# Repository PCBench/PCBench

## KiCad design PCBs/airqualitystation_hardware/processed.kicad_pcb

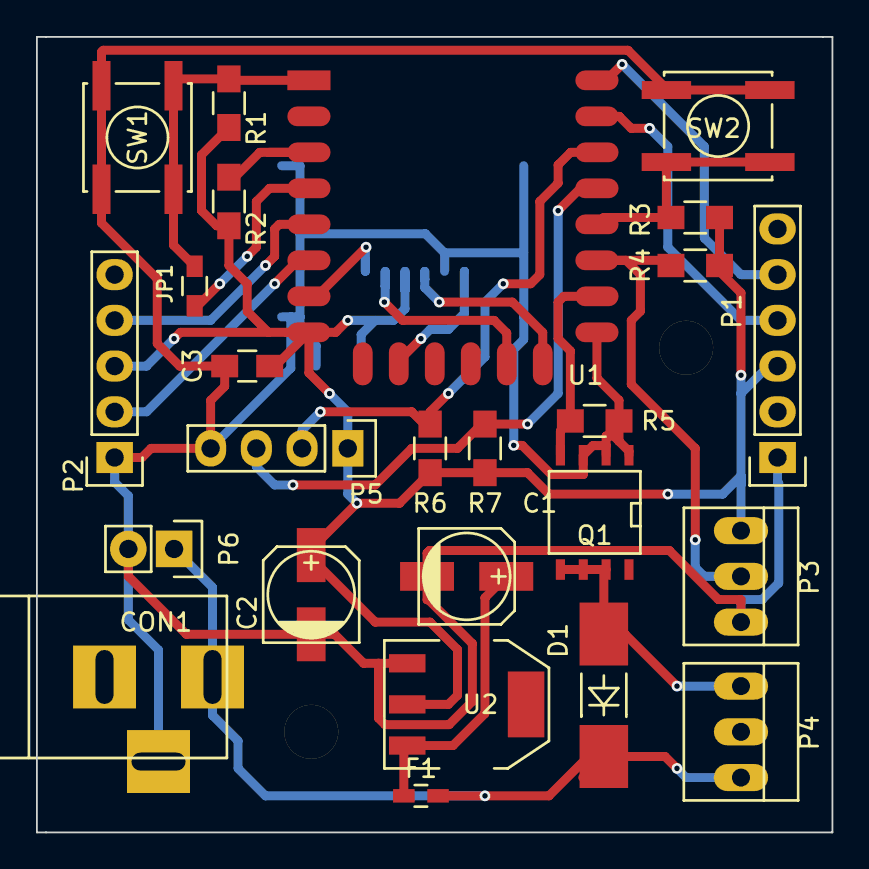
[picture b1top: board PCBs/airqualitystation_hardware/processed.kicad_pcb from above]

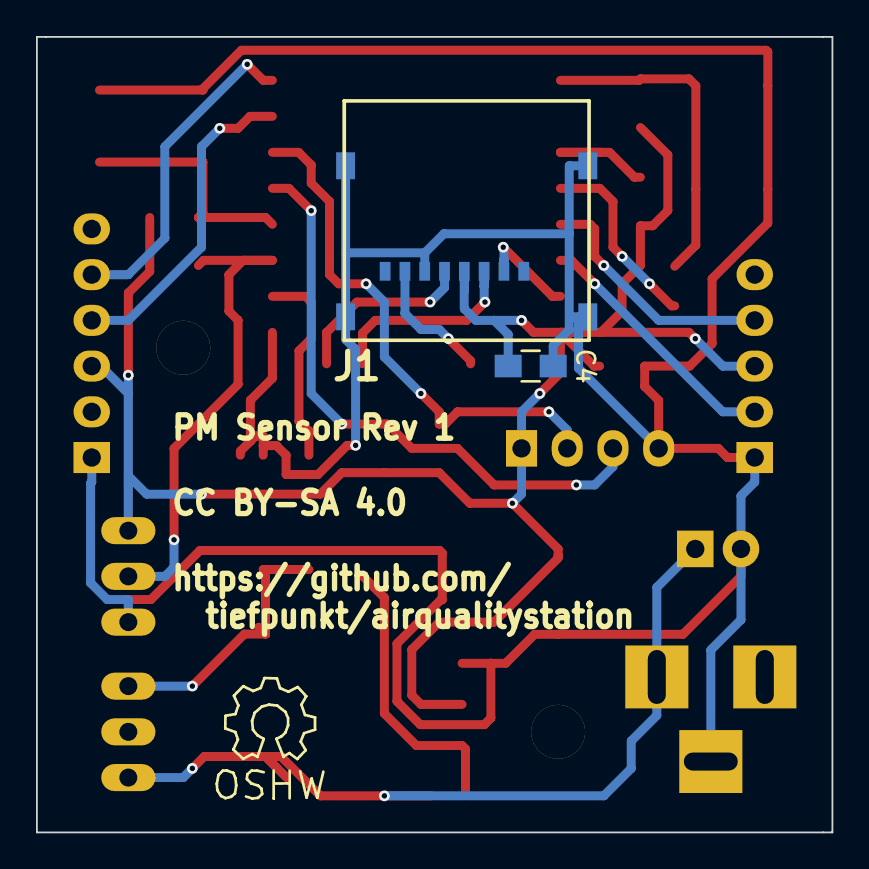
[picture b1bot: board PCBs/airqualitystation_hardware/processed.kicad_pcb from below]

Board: 2 copper layers, 44.2 x 44.2 mm, 27 parts (2 on the bottom side), 21 nets.

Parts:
C1, C2: 10µ; c_elec_5x5.3
C3, C4: 100n; C_0805_HandSoldering
CON1: Power; BARREL_JACK
D1: D; MELF_Handsoldering
F1: 0.1A; C_0603_HandSoldering
J1: MicroSD; MICRO_SD_HINGE_AMP
JP1: Sleep; R_0603_HandSoldering
P1: FTDI ESP; Pin_Header_Straight_1x06
P2: PPD42NS; Pin_Header_Straight_1x05
P3: DHT22; PINHEAD1-3
P4: Fan; PINHEAD1-3
P5: I2C; Pin_Header_Straight_1x04
P6: 5-9V; Pin_Header_Straight_1x02
Q1: IRF7401; SOIC-8-N
R1, R2, R3, R4, R5, R6, R7: 10k; R_0805_HandSoldering
SW1: Reset; SW_SPST_EVPBF
SW2: Flash; SW_SPST_EVPBF
U1: ESP-12E
U2: TS 1117 BCW33; SOT-223

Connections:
+9V: CON1.1, D1.1, F1.1, P4.3, P6.1
GND: C1.2, C2.2, C3.2, C4.2, CON1.3, J1.6, J1.SHLD, P1.1, P2.1, P3.3, P5.4, P6.2, Q1.1, Q1.2, Q1.3, R5.2, SW1.2, SW2.2, U1.15, U2.1
unnamed: C1.1, F1.2, U2.3
unnamed: D1.2, P4.1, Q1.5, Q1.6, Q1.7
unnamed: J1.2, U1.7
unnamed: J1.3, U1.13
unnamed: J1.5, U1.14
unnamed: J1.7, U1.10
unnamed: JP1.1, U1.4
unnamed: JP1.2, R1.2, SW1.1, U1.1
unnamed: P1.4, U1.21
unnamed: P1.5, U1.22
unnamed: P2.2, U1.6
unnamed: P2.4, U1.5
unnamed: P3.2, R4.2, U1.17
unnamed: P5.2, R6.2, U1.20
unnamed: P5.3, R7.2, U1.19
unnamed: Q1.4, R5.1, U1.16
unnamed: R2.2, U1.3
unnamed: R3.2, SW2.1, U1.18
VCC: C2.1, C3.1, C4.1, J1.4, P1.3, P2.3, P3.1, P5.1, R1.1, R2.1, R3.1, R4.1, R6.1, R7.1, U1.8, U2.2

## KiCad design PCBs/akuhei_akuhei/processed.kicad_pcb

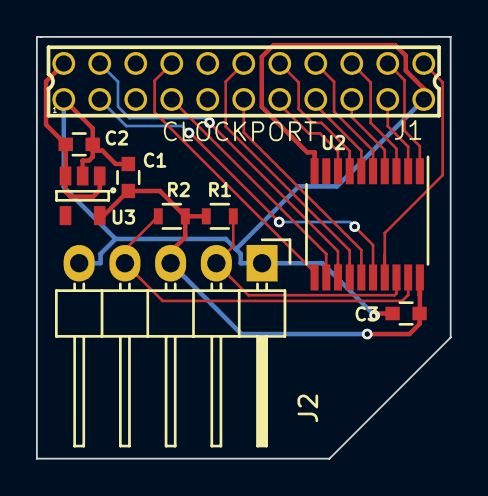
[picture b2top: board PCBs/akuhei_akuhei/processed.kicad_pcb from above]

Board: 2 copper layers, 23.0 x 23.4 mm, 9 parts (0 on the bottom side), 20 nets.

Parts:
C1: 1uF; C_0603
C2: 0.1uF; C_0603
C3: 100nF; C_0603
J1: CLOCKPORT; 87758-2216
J2: I2C; Pin_Header_Angled_1x05
R1, R2: 4.7k; R_0603
U2: PCA9564; TSSOP-20_4.4x6.5mm_Pitch0.65mm
U3: TLV70233DBV; SOT-23-5

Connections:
+3V3: C1.1, C3.1, J2.3, R1.2, R2.2, U2.20, U3.5
+5V: C2.1, J1.2, U3.1, U3.3
/A1: J1.12, U2.14
/A2: J1.11, U2.15
/D0: J1.20, U2.1
/D1: J1.19, U2.2
/D2: J1.18, U2.3
/D3: J1.17, U2.4
/D4: J1.16, U2.5
/D5: J1.15, U2.6
/D6: J1.14, U2.7
/D7: J1.13, U2.8
CP_CS: J1.4, U2.13
CP_INT: J1.3, U2.16
CP_IORD: J1.7, U2.12
CP_IOWR: J1.8, U2.11
CP_RESET: J1.22, U2.17
GND: C1.2, C2.2, C3.2, J1.1, J1.21, J2.1, J2.5, U2.10, U3.2
SCL: J2.2, R1.1, U2.18
SDA: J2.4, R2.1, U2.19

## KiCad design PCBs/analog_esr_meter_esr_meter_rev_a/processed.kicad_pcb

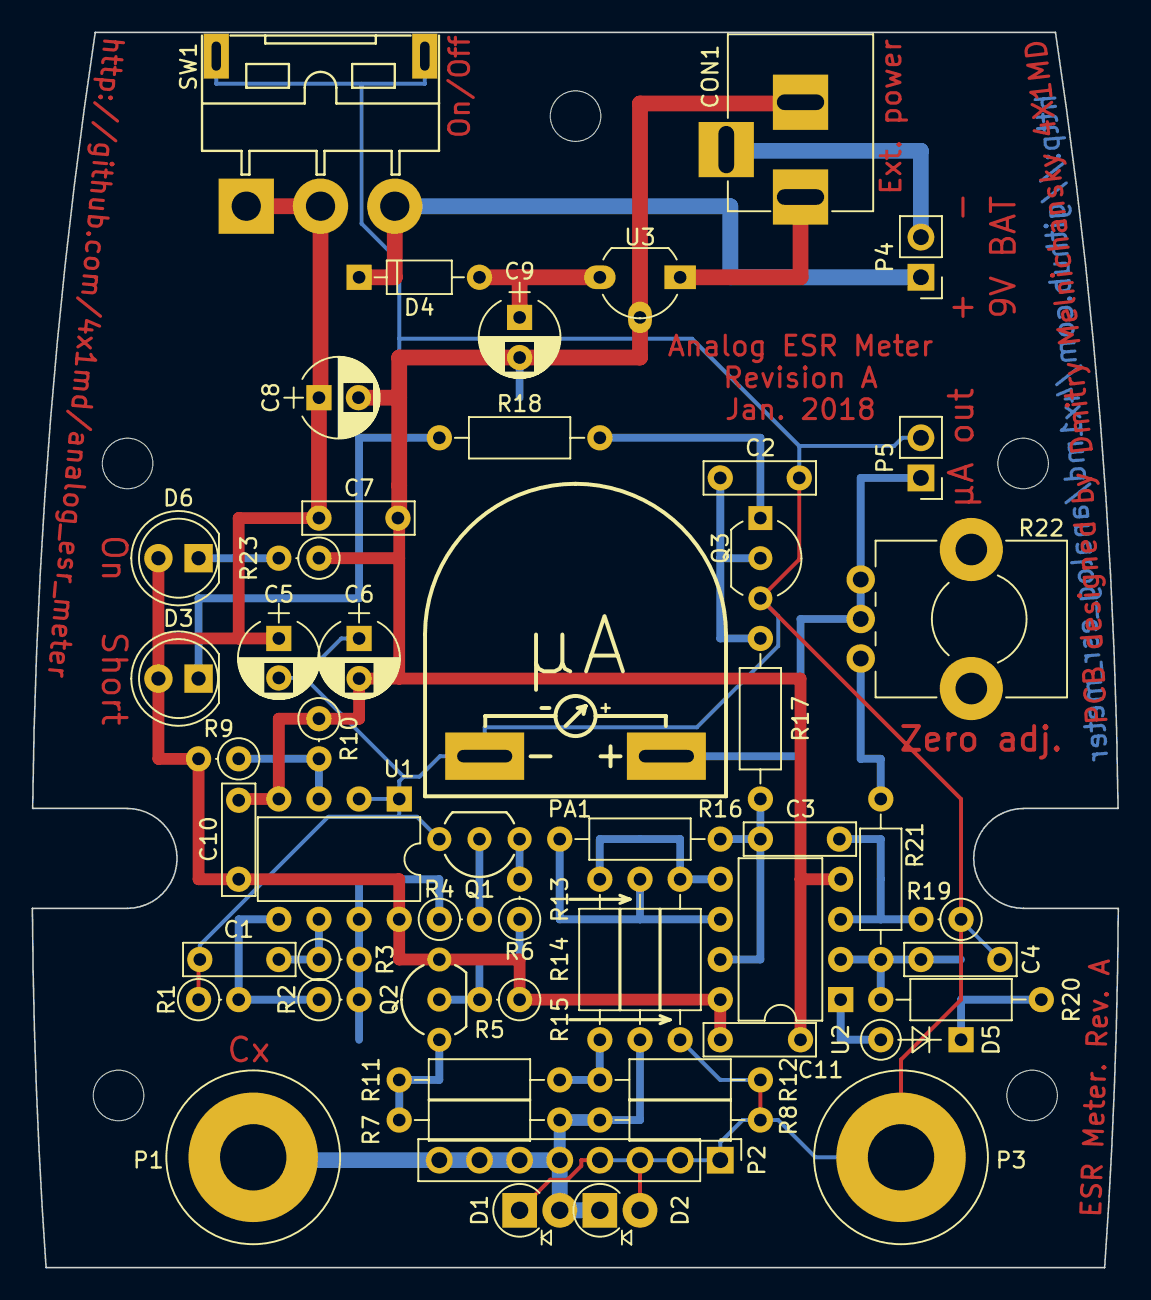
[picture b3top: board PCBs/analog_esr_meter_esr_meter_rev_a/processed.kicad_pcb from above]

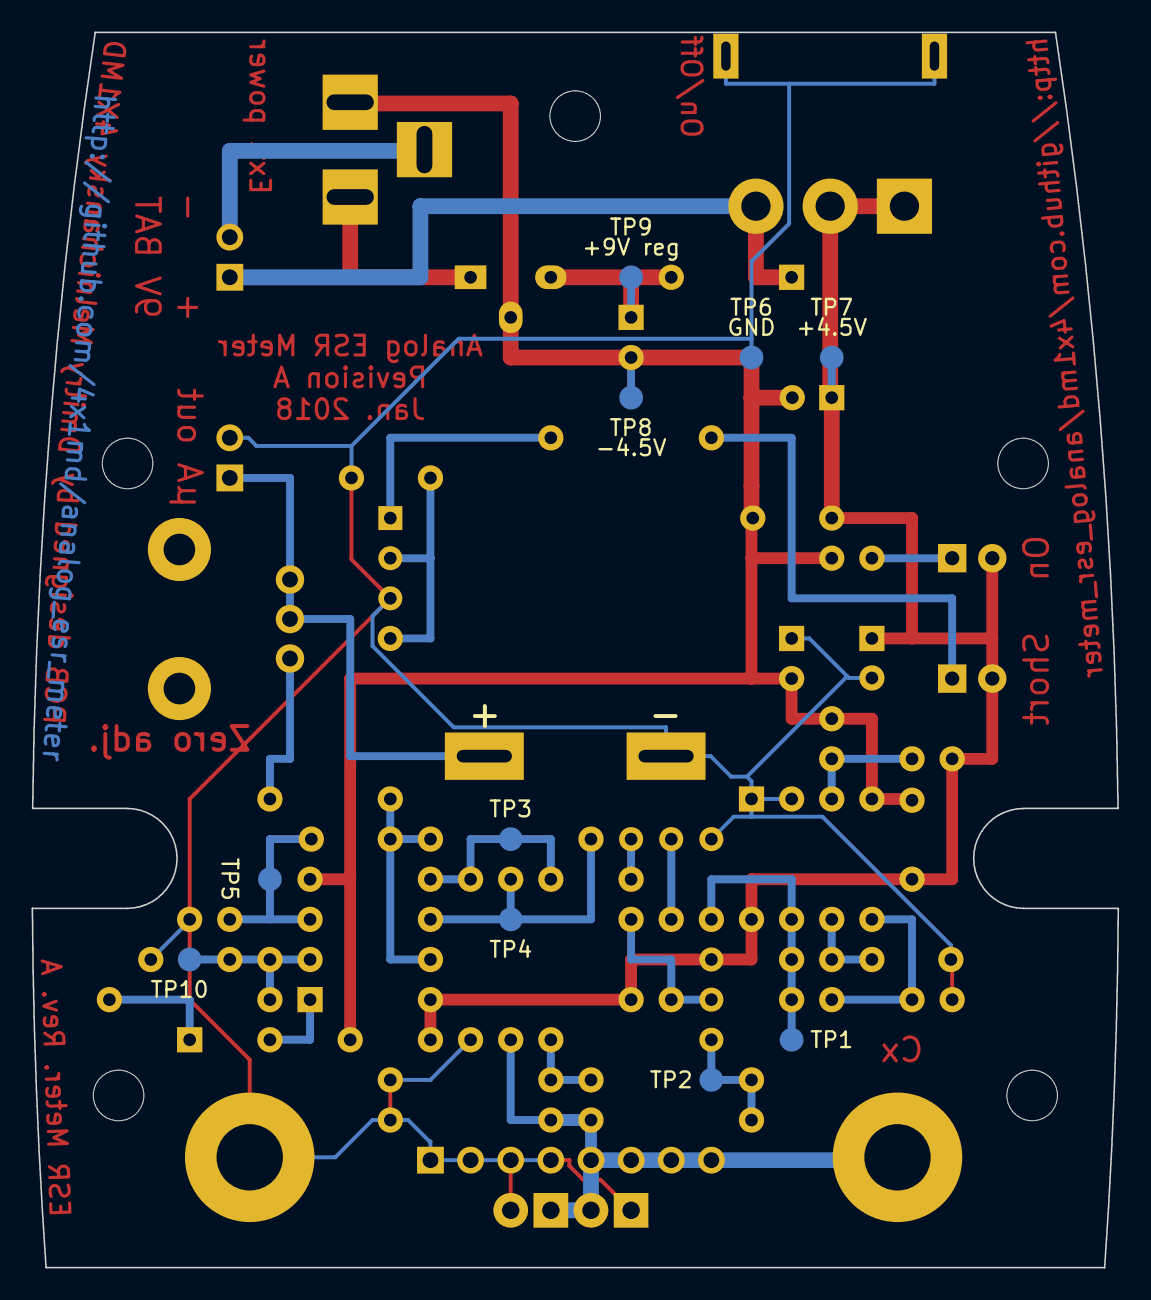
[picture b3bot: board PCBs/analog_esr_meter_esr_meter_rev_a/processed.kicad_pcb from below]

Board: 2 copper layers, 68.7 x 78.2 mm, 70 parts (10 on the bottom side), 30 nets.

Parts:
C1: 1nF; C_Rect_L7.0mm_W2.0mm_P5.00mm
C2, C4: 1uF; C_Rect_L7.0mm_W2.0mm_P5.00mm
C3, C7, C10, C11: 0.1uF; C_Rect_L7.0mm_W2.0mm_P5.00mm
C5, C6: 1uF; CP_Radial_D5.0mm_P2.50mm
C8: 22uF; CP_Radial_D5.0mm_P2.50mm
C9: 10uF; CP_Radial_D5.0mm_P2.50mm
CON1: External power; BARREL_JACK_PCB_EDGE
D1, D2: 1N4001; D_DO-41_SOD81_P2.54mm_Vertical_AnodeUp
D3: Red; LED_D5.0mm
D4: BAT60; D_DO-35_SOD27_P7.62mm_Horizontal
D5: 1N4148; D_DO-35_SOD27_P5.08mm_Vertical_KathodeUp
D6: Green; LED_D5.0mm
MH1, MH2, MH3, MH4, MH5: 3.2mm_M3_DIN965; MountingHole_3.2mm_M3_DIN965
MH**: 1.5mmx3.2mm_hole_for_wires
P1: Cx+; Banana_Jack_1Pin
P2: Cx; Socket_Strip_Straight_1x08_Pitch2.54mm
P3: Cx-; Banana_Jack_1Pin
P4: 9V battery; Pin_Header_Straight_1x02_Pitch2.54mm
P5: uA connector; Pin_Header_Straight_1x02_Pitch2.54mm
PA1: 50-250uA; Microampermeter
Q1, Q3: BC547; TO-92_Inline_Wide
Q2: BC557; TO-92_Inline_Wide
R1: 1.5K; R_Axial_DIN0207_L6.3mm_D2.5mm_P2.54mm_Vertical
R2, R3, R9, R10: 10K; R_Axial_DIN0207_L6.3mm_D2.5mm_P2.54mm_Vertical
R4: 68K; R_Axial_DIN0207_L6.3mm_D2.5mm_P2.54mm_Vertical
R5: 4.7K; R_Axial_DIN0207_L6.3mm_D2.5mm_P2.54mm_Vertical
R6: 12K; R_Axial_DIN0207_L6.3mm_D2.5mm_P2.54mm_Vertical
R7, R11, R13, R14, R21: 1K; R_Axial_DIN0207_L6.3mm_D2.5mm_P10.16mm_Horizontal
R8, R12: 22; R_Axial_DIN0207_L6.3mm_D2.5mm_P10.16mm_Horizontal
R15, R16: 47K; R_Axial_DIN0207_L6.3mm_D2.5mm_P10.16mm_Horizontal
R17: 15K; R_Axial_DIN0207_L6.3mm_D2.5mm_P10.16mm_Horizontal
R18: 470; R_Axial_DIN0207_L6.3mm_D2.5mm_P10.16mm_Horizontal
R19: 47K; R_Axial_DIN0207_L6.3mm_D2.5mm_P2.54mm_Vertical
R20: 47; R_Axial_DIN0207_L6.3mm_D2.5mm_P10.16mm_Horizontal
R22: 10K; Potentiometer_Alps_RK09K_Horizontal
R23: 470; R_Axial_DIN0207_L6.3mm_D2.5mm_P2.54mm_Vertical
SW1: On/Off; Switch_Slide_SPDT_THT_5MS1S102AM6QES
TP1: Osc. out; Measurement_Point_Round-SMD-Pad_Small
TP2: Bridge; Measurement_Point_Round-SMD-Pad_Small
TP3: Amp. (+); Measurement_Point_Round-SMD-Pad_Small
TP4: Amp (-); Measurement_Point_Round-SMD-Pad_Small
TP5: Amp. out; Measurement_Point_Round-SMD-Pad_Small
TP6: GND; Measurement_Point_Round-SMD-Pad_Small
TP7: +4.5V; Measurement_Point_Round-SMD-Pad_Small
TP8: -4.5V; Measurement_Point_Round-SMD-Pad_Small
TP9: +9V reg; Measurement_Point_Round-SMD-Pad_Small
TP10: Vout; Measurement_Point_Round-SMD-Pad_Small
U1, U2: TL082; DIP-8_W7.62mm
U3: LM7809CT; TO-92_Molded_Wide_Oval

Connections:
/+4.5V: C5.1, C7.1, C8.1, C10.1, C11.1, D3.2, D6.2, Q2.3, R5.1, R9.2, SW1.1, SW1.2, TP7.1, U1.8, U2.8
/+9V: D4.1, P4.1, SW1.3
/+9V_REG: C9.1, D4.2, TP9.1, U3.3
/-4.5V: C6.2, C7.2, C8.2, C9.2, C10.2, C11.2, CON1.2, R10.1, R23.1, TP8.1, U1.4, U2.4, U3.2
/CX: D1.2, D2.1, P1.1, P2.5, P2.6, P2.7, P2.8, R7.1, R8.1, R13.1
/EXT_VIN: CON1.1, U3.1
GNDREF: C1.2, C2.2, C4.2, C5.2, C6.1, D1.1, D2.2, P2.1, P2.2, P2.3, P2.4, P3.1, P5.2, PA1.2, Q1.3, Q3.3, R1.1, R8.2, R12.2, R15.1, R19.1, SW1.4, TP6.1, U1.1, U1.2
unnamed: C1.1, R3.1, U1.6
unnamed: C2.1, Q3.2, R17.1
unnamed: C3.1, R16.2, R17.2, U2.7
unnamed: C3.2, R19.2, TP5.1, U2.3
unnamed: C4.1, R20.1, R21.2, TP10.1, U2.2
unnamed: CON1.3, P4.2
unnamed: D3.1, R18.2
unnamed: D5.1, R20.2
unnamed: D5.2, U2.1
unnamed: D6.1, R23.2
unnamed: P5.1, PA1.1, R22.2, R22.3
unnamed: Q1.1, R6.2
unnamed: Q1.2, R4.2
unnamed: Q2.1, R7.2, R11.2, TP2.1
unnamed: Q2.2, R5.2, R6.1
unnamed: Q3.1, R18.1
unnamed: R1.2, R2.1, U1.5
unnamed: R2.2, R3.2, R4.1, TP1.1, U1.7
unnamed: R9.1, R10.2, U1.3
unnamed: R11.1, R12.1, R14.1
unnamed: R13.2, R16.1, TP4.1, U2.6
unnamed: R14.2, R15.2, TP3.1, U2.5
unnamed: R21.1, R22.1

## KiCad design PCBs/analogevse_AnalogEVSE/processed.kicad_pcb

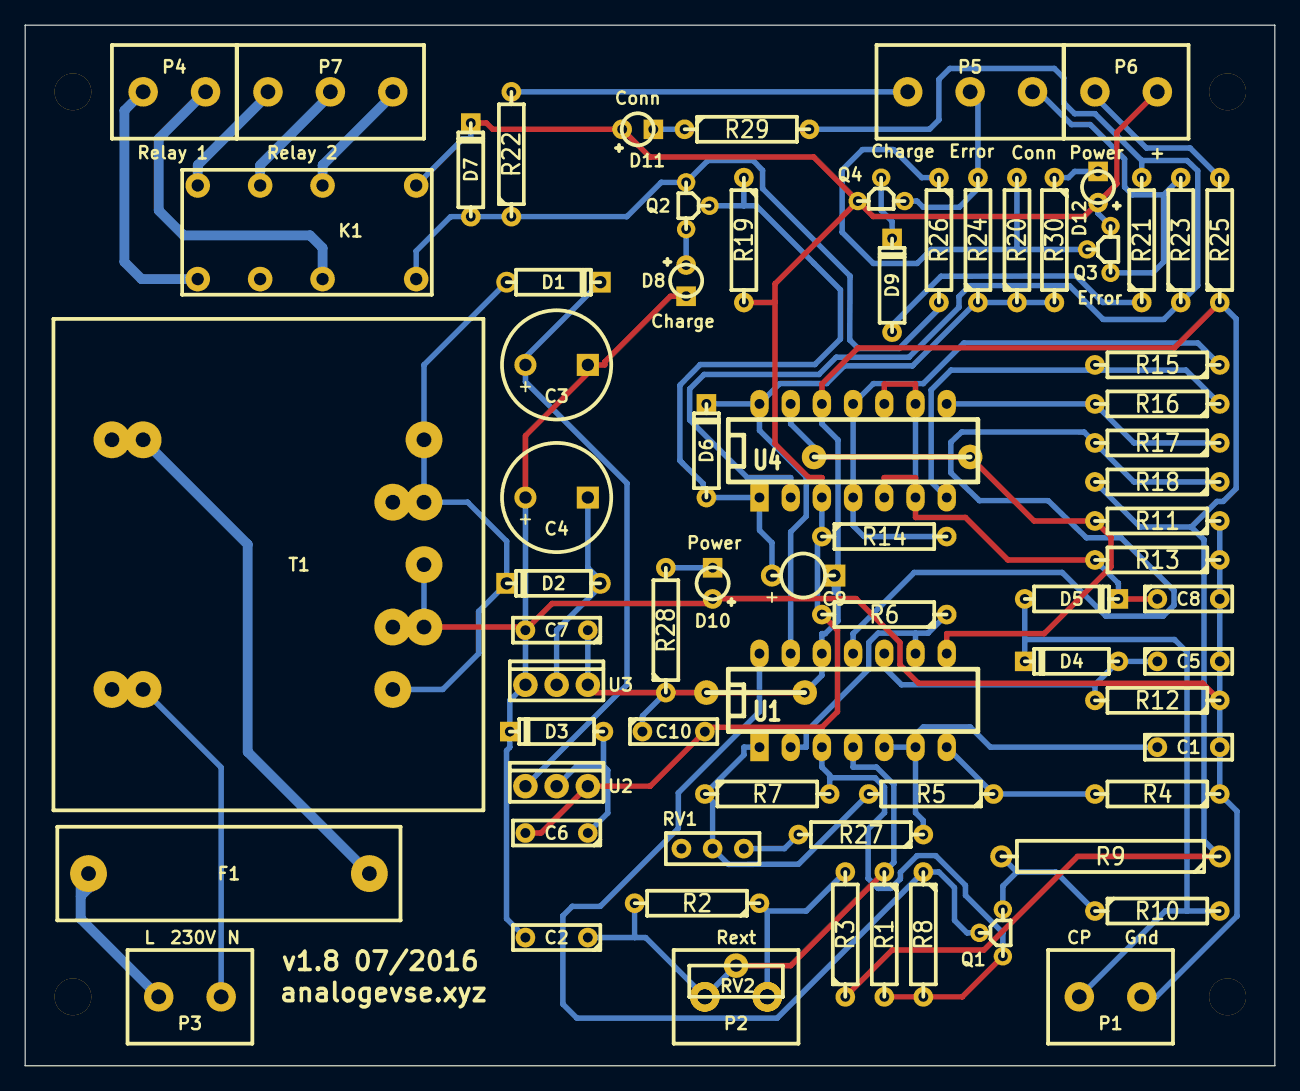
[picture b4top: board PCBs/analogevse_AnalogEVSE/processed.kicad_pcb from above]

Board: 2 copper layers, 101.7 x 84.7 mm, 80 parts (0 on the bottom side), 47 nets.

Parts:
C1: 5n6; C2
C2, C5, C6, C8: 100n; C2
C3, C4: 220u/25V; C5
C7: 220n; C2
C9: 4u7/16V; C6
C10: 150n; C2
D1, D2: 1N4002; D3-big
D3, D4, D5, D6, D7: 1N4148; D3
D8: Charging; LED-3
D9: SD101C; D3
D10: Power; LED-3
D11: Conn; LED-3
D12: Error; LED-3
F1: 100mA; Fuse-RM9
K1: Relay
Noname_1, Noname_2, Noname_3, Noname_8: WireBridgePad; DrillPad-3mm
Noname_4, Noname_5, Noname_6, Noname_7: WireBridgePad
P1: Pilot; Term-2pin
P2: Rext; Term-2pin
P3: 230V; Term-2pin
P4: Relay 1; Term-2pin
P5: Status LEDs; Term-3pin
P6: Power; Term-2pin
P7: Relay 2; Term-3pin
Q1, Q2, Q4: BC337-40; TO92
Q3: BC557; TO92
R1, R16: 5k6; R4-LARGE_PADS
R2, R6, R7, R8, R11, R21: 10k; R4-LARGE_PADS
R3: 1k5; R4-LARGE_PADS
R4, R5, R20, R26: 100k; R4-LARGE_PADS
R9: 1k/1W; R8
R10, R18: 1k; R4-LARGE_PADS
R12, R13: 1M; R4-LARGE_PADS
R14, R23, R24, R25, R28, R29, R30: 4k7; R4-LARGE_PADS
R15: 3k3; R4-LARGE_PADS
R17: 15k; R4-LARGE_PADS
R19, R27: 47k; R4-LARGE_PADS
R22: 2k2; R4-LARGE_PADS
RV1: 100k; Trimpot
RV2: 10k; Trimpot3
T1: 12V/3VA; Printtrafo
U1, U4: LM2901; IC-DIP-14
U2: LM7812
U3: LM7912

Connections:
+12V: C6.2, C10.2, D7.2, D11.1, D12.1, K1.9, P6.1, Q1.3, Q3.1, Q4.3, R1.2, R6.2, R7.2, R8.2, R14.1, R19.2, U1.3, U2.VO, U4.3
-12V: C7.1, C9.2, C10.1, Noname_4.2, Noname_5.2, R3.1, R9.1, R18.2, R25.1, R28.1, U1.12, U3.VO, U4.12
GND: C1.2, C2.2, C3.2, C4.1, C5.2, C7.2, C8.2, D3.2, D8.2, D10.1, P1.2, R4.1, R11.1, R12.1, R13.1, T1.4, U3.GND
unnamed: C1.1, R27.1, U1.5, U1.6
unnamed: C2.1, P2.1, R1.1, R2.2, RV2.1, RV2.2, U1.4
unnamed: C3.1, D1.2, U2.VI
unnamed: C4.2, D2.1, U3.VI
unnamed: C5.1, D4.1, R12.2, U1.10
unnamed: C6.1, D3.1, U2.GND
unnamed: C8.1, D5.2, R13.2, U4.5, U4.6, U4.9, U4.10
unnamed: C9.1, D6.1, Q2.2, R19.1, U4.1
unnamed: D1.1, D2.2, T1.3
unnamed: D4.2, D5.1, P1.1, R10.2
unnamed: D6.2, R20.1, R24.1, R30.2, U1.13, U4.14
unnamed: D7.1, K1.8, Q2.3, R22.1, R26.2
unnamed: D8.1, Q2.1
unnamed: D9.1, R21.1
unnamed: D9.2, Q4.2
unnamed: D10.2, R28.2
unnamed: D11.2, R29.1
unnamed: D12.2, R30.1
unnamed: F1.1, P3.1
unnamed: F1.2, T1.2
unnamed: K1.1, P4.2
unnamed: K1.5, P4.1
unnamed: K1.12, P7.1
unnamed: K1.14, P7.2
unnamed: K1.16, P7.3
unnamed: P2.2, R2.1, R3.2, RV2.3
unnamed: P3.2, T1.1
unnamed: P5.1, R22.2
unnamed: P5.2, Q4.1, R24.2
unnamed: P5.3, Q3.3, R23.2
unnamed: P6.2, R25.2
unnamed: Q1.1, R9.2, R10.1
unnamed: Q1.2, R8.1, U1.14
unnamed: Q3.2, R20.2, R26.1
unnamed: R4.2, R5.1, U1.7
unnamed: R5.2, R7.1, RV1.2, U1.1
unnamed: R6.1, U1.2, U1.9
unnamed: Noname_6.2, Noname_7.2, R11.2, U1.8, U4.13
unnamed: R21.2, R23.1, R29.2, U4.2
unnamed: R27.2, RV1.3
Vcharge: R15.2, R16.1, U4.7
Vconn: R14.2, R15.1, U4.4, U4.11
Vmin: R16.2, R17.1, U4.8
Vneg: R17.2, R18.1, U1.11

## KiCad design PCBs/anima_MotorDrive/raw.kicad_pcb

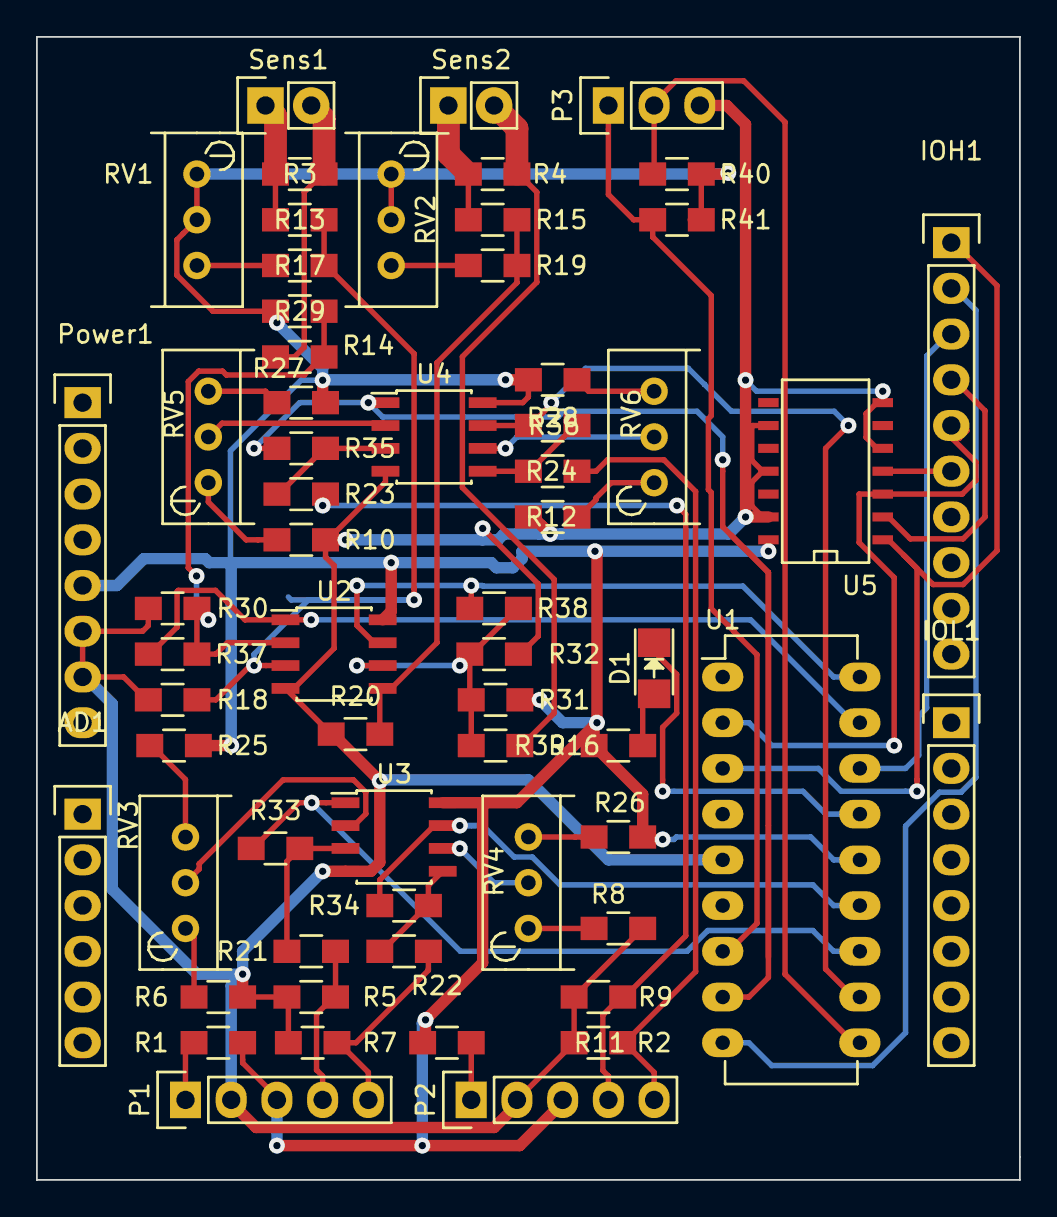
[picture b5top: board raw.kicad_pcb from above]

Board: 2 copper layers, 54.6 x 63.5 mm, 62 parts (0 on the bottom side), 50 nets.

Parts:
AD1: CONN_01X06; Pin_Header_Straight_1x06
D1: LED; LED-1206
IOH1: CONN_01X10; Pin_Header_Straight_1x10
IOL1: CONN_01X08; Pin_Header_Straight_1x08
P1, P2: CONN_01X05; Pin_Header_Straight_1x05
P3: CONN_01X03; Pin_Header_Straight_1x03
Power1: CONN_01X08; Pin_Header_Straight_1x08
R1, R2, R3, R4, R5, R6, R7, R8, R9, R10, R11, R12, R13, R14, R15, R16, R17, R18, R19, R20, R21, R22, R23, R24, R25, R26, R27, R28, R29, R30, R31, R32, R33, R34, R35, R36, R37, R38, R39, R40, R41: R; R_0805_HandSoldering
RV1, RV2, RV3, RV4, RV5, RV6: POT; Potentiometer_Bourns_3296W_3-8Zoll_Inline_ScrewUp
Sens1, Sens2: CONN_01X02; Pin_Header_Straight_1x02
U1: PIC16(L)F1847-I/P; DIP-18_W7.62mm_LongPads
U2, U3, U4: LM358N; SOIC-8_3.9x4.9mm_Pitch1.27mm
U5: 74HC04; SOIC-14_N

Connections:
+5V: P1.3, P2.3, Power1.5, R1.1, R2.1, R25.2, R26.2, R27.2, R28.2, R29.2, R31.2, R39.1, R40.1, R41.1, RV1.1, RV1.2, RV2.1, RV2.2, U1.14, U2.8, U3.8, U4.8, U5.14
GND: P1.2, P2.2, P3.3, Power1.6, Power1.7, R5.1, R6.2, R7.1, R8.2, R9.1, R10.2, R11.1, R12.2, R18.1, R20.1, R30.1, R32.1, U1.5, U2.4, U3.4, U4.4, U5.5, U5.7, U5.9, U5.11, U5.13
unnamed: D1.1, U1.15
unnamed: D1.2, R39.2
unnamed: IOH1.1, U1.3, U5.1
unnamed: IOH1.2, U1.9
unnamed: IOH1.3, U1.16
unnamed: IOH1.4, U5.2
unnamed: IOH1.5, U1.2, U5.3
unnamed: IOH1.6, U5.4
unnamed: P1.1, R1.2
unnamed: P1.4, R5.2, R21.2
unnamed: P1.5, R7.2, R22.2
unnamed: P2.1, R2.2
unnamed: P2.4, R9.2, R23.2
unnamed: P2.5, R11.2, R24.2
unnamed: P3.1, R41.2, U1.7
unnamed: P3.2, R40.2, U1.10
unnamed: R6.1, RV3.1
unnamed: R8.1, RV4.1
unnamed: R10.1, RV5.1
unnamed: R12.1, RV6.1
unnamed: R13.1, R17.1, R18.2, U2.3
unnamed: R3.2, R13.2, Sens1.1
unnamed: R14.1, R29.1, R30.2, R37.2, U2.2
unnamed: R3.1, R14.2, Sens1.2
unnamed: R15.1, R19.1, R20.2, U2.5
unnamed: R4.2, R15.2, Sens2.1
unnamed: R16.1, R31.1, R32.2, R38.2, U2.6
unnamed: R4.1, R16.2, Sens2.2
unnamed: R17.2, RV1.3
unnamed: R19.2, RV2.3
unnamed: R21.1, R33.2, U3.3
unnamed: R22.1, R34.2, U3.5
unnamed: R23.1, R35.2, U4.3
unnamed: R24.1, R36.2, U4.5
unnamed: R25.1, RV3.3
unnamed: R26.1, RV4.3
unnamed: R27.1, RV5.3
unnamed: R28.1, RV6.3
unnamed: R33.1, U1.12, U3.1
unnamed: R34.1, U1.13, U3.7
unnamed: R35.1, U1.8, U4.1
unnamed: R36.1, U1.11, U4.7
unnamed: R37.1, U1.17, U2.1
unnamed: R38.1, U1.18, U2.7
unnamed: RV3.2, U3.2
unnamed: RV4.2, U3.6
unnamed: RV5.2, U4.2
unnamed: RV6.2, U4.6

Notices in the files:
PCBs/airqualitystation_hardware/processed.kicad_pcb:
CC BY-SA 4.0
